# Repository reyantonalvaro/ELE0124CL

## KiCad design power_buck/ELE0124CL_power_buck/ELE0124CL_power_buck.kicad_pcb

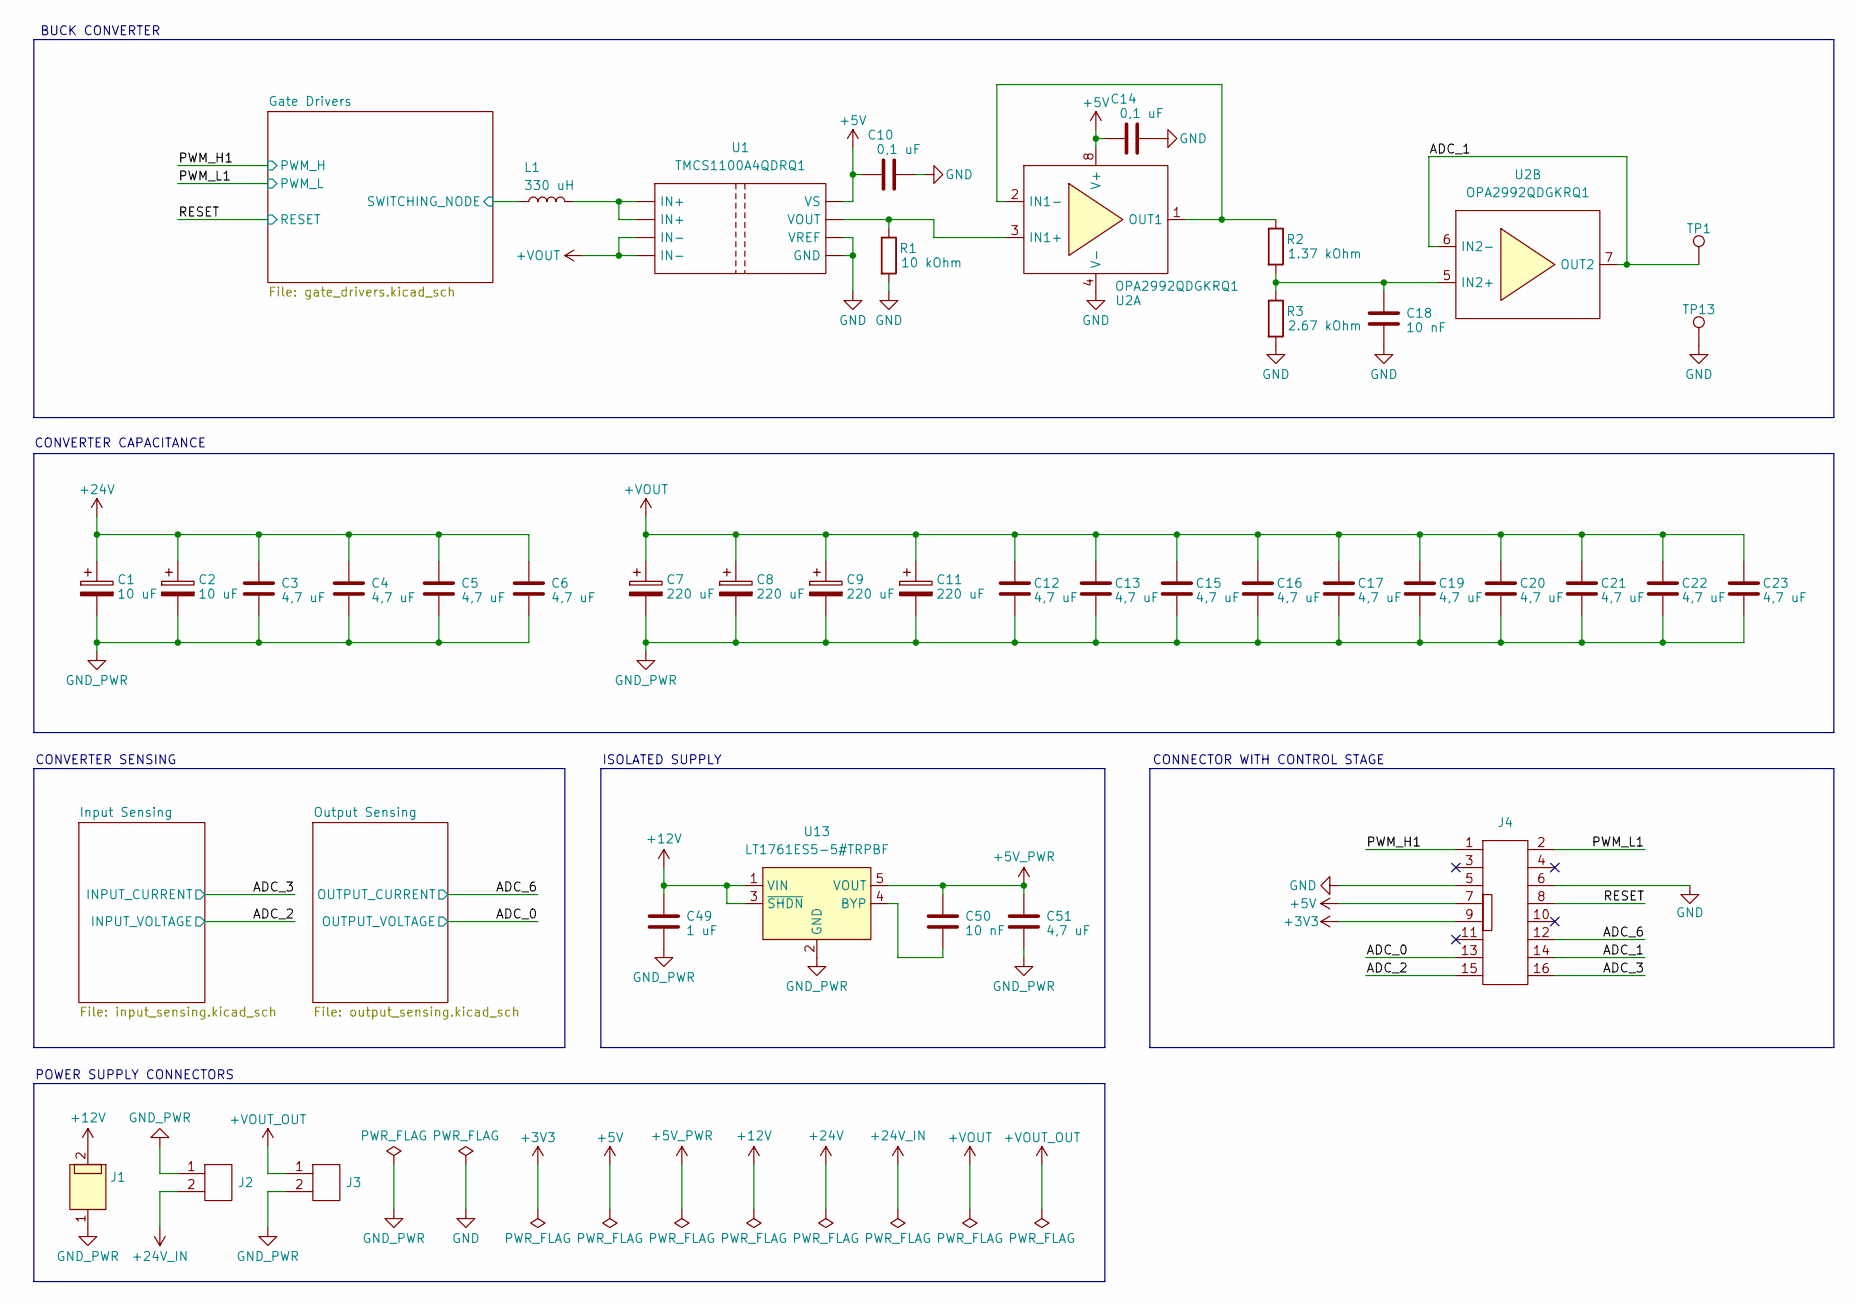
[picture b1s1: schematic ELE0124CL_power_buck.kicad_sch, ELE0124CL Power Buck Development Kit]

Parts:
C1, C2: 10 uF; C_D5.0mm_H11.0mm_P2.00mm
C3, C4, C5, C6, C12, C13, C15, C16, C17, C19, C20, C21, C22, C23, C51: 4,7 uF; C_1206_3216Metric
C7, C8, C9, C11: 220 uF; C_D10.0mm_H16.0mm_P5.00mm
C10, C14: 0,1 uF; C_0603_1608Metric
C18, C50: 10 nF; C_0603_1608Metric
C49: 1 uF; C_1206_3216Metric
J1: 43045-0212; CONN_SOCKET_1x02_P3.00mm_Vertical
J2, J3: MSTBVA 2,5/ 2-G-5,08; CONN_TERMINAL_BLOCK_1x02_P5.08mm_Vertical
J4: 878311620; CONN_SOCKET_2x08_P2.00mm_Vertical
L1: 330 uH; L_74437529203331
R1: 10 kOhm; R_0603_1608Metric
R2: 1.37 kOhm; R_0603_1608Metric
R3: 2.67 kOhm; R_0603_1608Metric
TP1, TP13: TP_THT
U1: TMCS1100A4QDRQ1; SOIC-8_5.40mm_P1.27mm
U2: OPA2992QDGKRQ1; VSSOP-8_4.40mm_P0.65mm
U13: LT1761ES5-5#TRPBF; TSOT-23-5

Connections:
+3V3: J4.9; also elsewhere on the board
+5V: C10.1, C14.1, J4.7, U1.8 (VS), U2.8 (V+); also elsewhere on the board
+5V_PWR: C50.1, C51.1, U13.5 (VOUT); also elsewhere on the board
+12V: C49.1, J1.2, U13.1 (VIN), U13.3 (~SHDN); also elsewhere on the board
+24V: C1.1, C2.1, C3.1, C4.1, C5.1, C6.1; also elsewhere on the board
+24V_IN: J2.2; also elsewhere on the board
+VOUT: C7.1, C8.1, C9.1, C11.1, C12.1, C13.1, C15.1, C16.1, C17.1, C19.1, C20.1, C21.1, C22.1, C23.1, U1.3 (IN-), U1.4 (IN-); also elsewhere on the board
+VOUT_OUT: J3.1; also elsewhere on the board
/ADC_0: J4.13; also elsewhere on the board
/ADC_1: J4.14, TP1.1 (TP), U2.6 (IN2-), U2.7 (OUT2)
/ADC_2: J4.15; also elsewhere on the board
/ADC_3: J4.16; also elsewhere on the board
/ADC_6: J4.12; also elsewhere on the board
/Gate Drivers/SWITCHING_NODE: L1.1; also elsewhere on the board
/PWM_H1: J4.1; also elsewhere on the board
/PWM_L1: J4.2; also elsewhere on the board
/RESET: J4.8; also elsewhere on the board
GND: C10.2, C14.2, C18.2, J4.5, J4.6, R1.2, R3.2, TP13.1 (TP), U1.5 (GND), U1.6 (VREF), U2.4 (V-); also elsewhere on the board
GND_PWR: C1.2, C2.2, C3.2, C4.2, C5.2, C6.2, C7.2, C8.2, C9.2, C11.2, C12.2, C13.2, C15.2, C16.2, C17.2, C19.2, C20.2, C21.2, C22.2, C23.2, C49.2, C51.2, J1.1, J2.1, J3.2, U13.2 (GND); also elsewhere on the board
unnamed: L1.2, U1.1 (IN+), U1.2 (IN+)
unnamed: R1.1, U1.7 (VOUT), U2.3 (IN1+)
unnamed: R2.1, U2.1 (OUT1), U2.2 (IN1-)
unnamed: C18.1, R2.2, R3.1, U2.5 (IN2+)
unnamed: C50.2, U13.4 (BYP)

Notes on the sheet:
CONNECTOR WITH CONTROL STAGE
CONVERTER CAPACITANCE
CONVERTER SENSING
BUCK CONVERTER
ISOLATED SUPPLY
POWER SUPPLY CONNECTORS

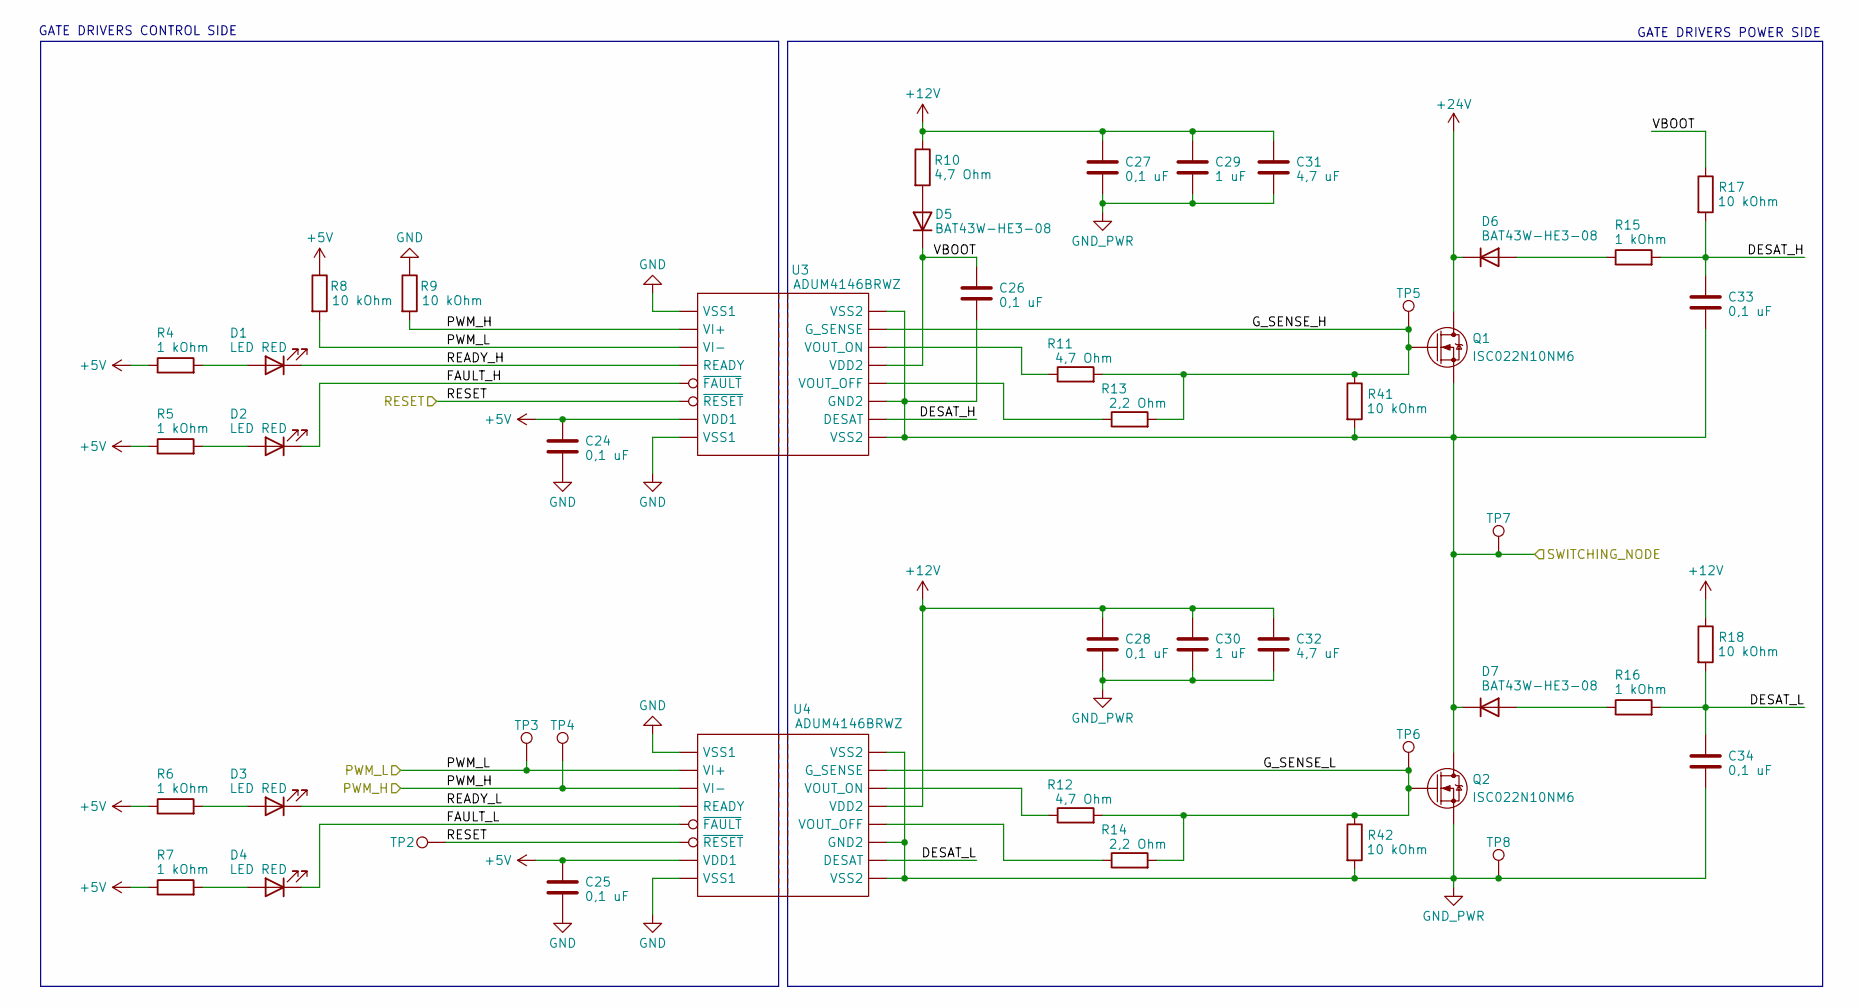
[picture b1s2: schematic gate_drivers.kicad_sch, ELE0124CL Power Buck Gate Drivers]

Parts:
C24, C25, C27, C28, C33, C34: 0,1 uF; C_0603_1608Metric
C26: 0,1 uF; C_1206_3216Metric
C29, C30: 1 uF; C_1206_3216Metric
C31, C32: 4,7 uF; C_1206_3216Metric
D1, D2, D3, D4: LED RED; D_0603_1608Metric
D5, D6, D7: BAT43W-HE3-08; D_SOD-123
Q1, Q2: ISC022N10NM6; PG-TDSON-8-3
R4, R5, R6, R7, R15, R16: 1 kOhm; R_0603_1608Metric
R8, R9, R17, R18, R41, R42: 10 kOhm; R_0603_1608Metric
R10, R11, R12: 4,7 Ohm; R_2512_6332Metric
R13, R14: 2,2 Ohm; R_2512_6332Metric
TP2, TP3, TP4: TP_D1.0mm
TP5, TP6, TP7, TP8: TP_THT
U3, U4: ADUM4146BRWZ; SOIC-16W_9.60mm_P1.27mm

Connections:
+5V: C24.1, C25.1, R4.1, R5.1, R6.1, R7.1, R8.1, U3.7 (VDD1), U4.7 (VDD1); also elsewhere on the board
+12V: C27.1, C28.1, C29.1, C30.1, C31.1, C32.1, R10.1, R18.1, U4.13 (VDD2); also elsewhere on the board
+24V: D6.1 (K), Q1.3 (D); also elsewhere on the board
/Gate Drivers/DESAT_H: C33.1, R15.2, R17.2, U3.10 (DESAT)
/Gate Drivers/DESAT_L: C34.1, R16.2, R18.2, U4.10 (DESAT)
/Gate Drivers/FAULT_H: D2.1 (K), U3.5 (~FAULT)
/Gate Drivers/FAULT_L: D4.1 (K), U4.5 (~FAULT)
/Gate Drivers/G_SENSE_H: Q1.2 (G), R11.2, R13.2, R41.1, TP5.1 (TP), U3.15 (G_SENSE)
/Gate Drivers/G_SENSE_L: Q2.2 (G), R12.2, R14.2, R42.1, TP6.1 (TP), U4.15 (G_SENSE)
/Gate Drivers/READY_H: D1.1 (K), U3.4 (READY)
/Gate Drivers/READY_L: D3.1 (K), U4.4 (READY)
/Gate Drivers/SWITCHING_NODE: C26.2, C33.2, D7.1 (K), Q1.1 (S), Q2.3 (D), R41.2, TP7.1 (TP), U3.9 (VSS2), U3.11 (GND2), U3.16 (VSS2); also elsewhere on the board
/Gate Drivers/VBOOT: C26.1, D5.1 (K), R17.1, U3.13 (VDD2)
/PWM_H1: R9.2, TP4.1 (TP), U3.2 (VI+), U4.3 (VI-); also elsewhere on the board
/PWM_L1: R8.2, TP3.1 (TP), U3.3 (VI-), U4.2 (VI+); also elsewhere on the board
/RESET: TP2.1 (TP), U3.6 (~RESET), U4.6 (~RESET); also elsewhere on the board
GND: C24.2, C25.2, R9.1, U3.1 (VSS1), U3.8 (VSS1), U4.1 (VSS1), U4.8 (VSS1); also elsewhere on the board
GND_PWR: C27.2, C28.2, C29.2, C30.2, C31.2, C32.2, C34.2, Q2.1 (S), R42.2, TP8.1 (TP), U4.9 (VSS2), U4.11 (GND2), U4.16 (VSS2); also elsewhere on the board
unnamed: D1.2 (A), R4.2
unnamed: D2.2 (A), R5.2
unnamed: D3.2 (A), R6.2
unnamed: D4.2 (A), R7.2
unnamed: D5.2 (A), R10.2
unnamed: D6.2 (A), R15.1
unnamed: D7.2 (A), R16.1
unnamed: R13.1, U3.12 (VOUT_OFF)
unnamed: R11.1, U3.14 (VOUT_ON)
unnamed: R14.1, U4.12 (VOUT_OFF)
unnamed: R12.1, U4.14 (VOUT_ON)

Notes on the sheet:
GATE DRIVERS CONTROL SIDE
GATE DRIVERS POWER SIDE

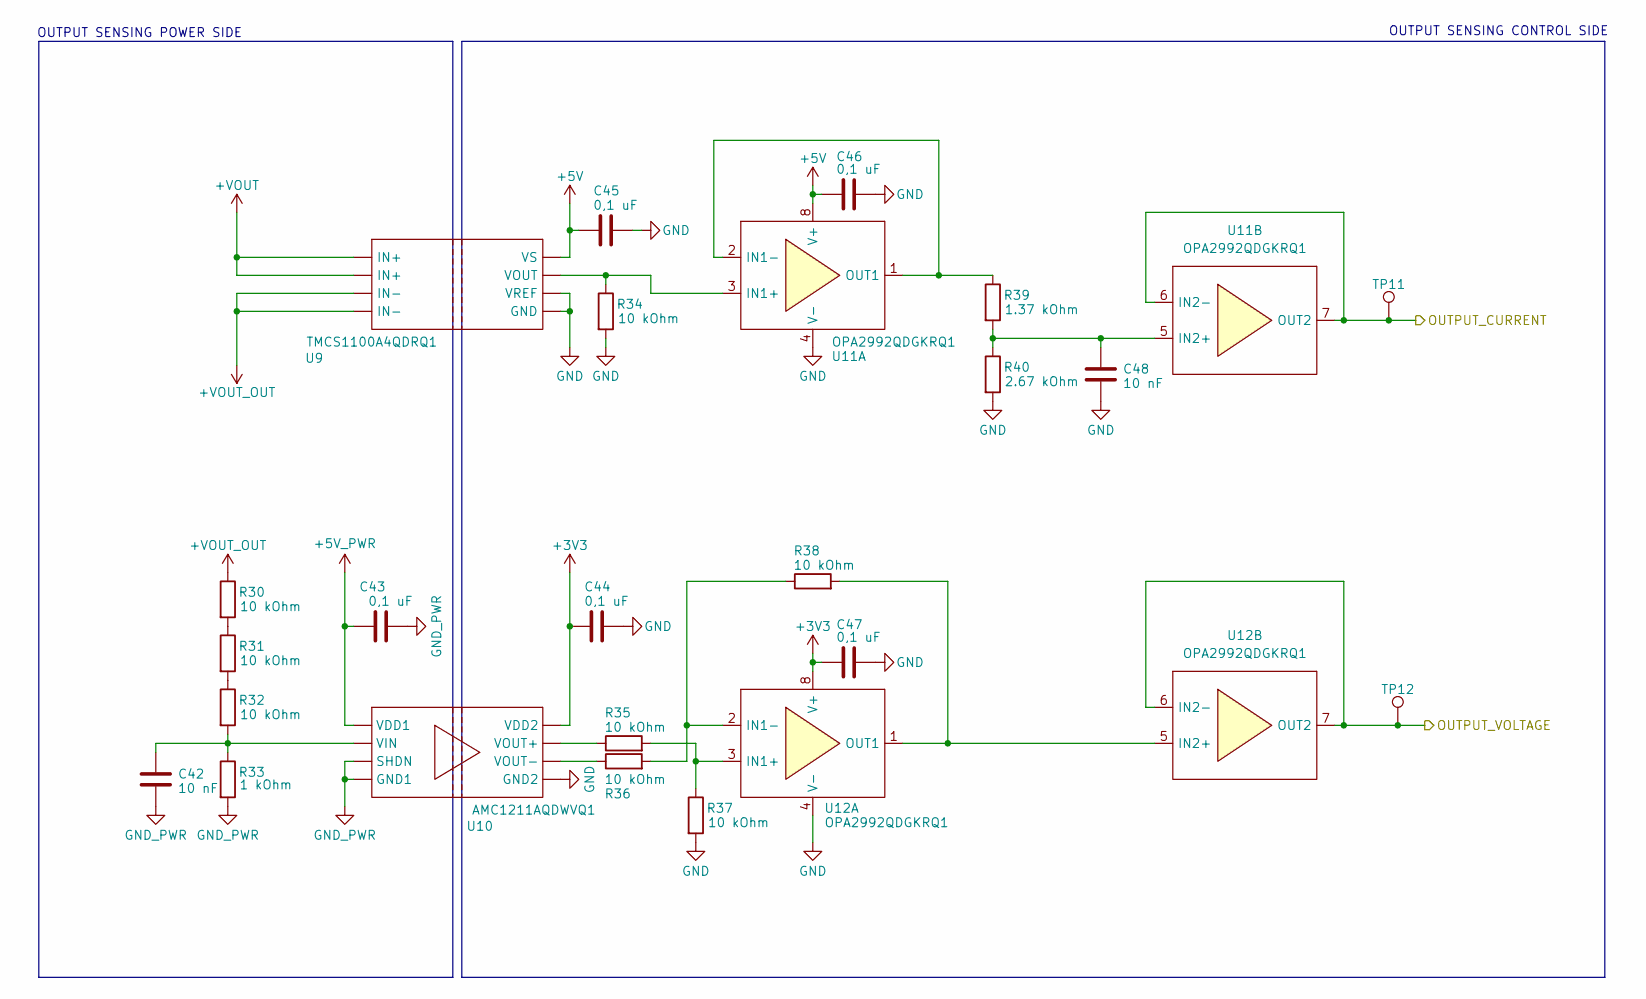
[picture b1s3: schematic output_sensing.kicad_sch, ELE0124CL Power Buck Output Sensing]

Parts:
C42, C48: 10 nF; C_0603_1608Metric
C43, C44, C45, C46, C47: 0,1 uF; C_0603_1608Metric
R30, R31, R32, R34, R35, R36, R37, R38: 10 kOhm; R_0603_1608Metric
R33: 1 kOhm; R_0603_1608Metric
R39: 1.37 kOhm; R_0603_1608Metric
R40: 2.67 kOhm; R_0603_1608Metric
TP11, TP12: TP_D1.0mm
U9: TMCS1100A4QDRQ1; SOIC-8_5.40mm_P1.27mm
U10: AMC1211AQDWVQ1; SSO-8_10.80mm_P1.27mm
U11, U12: OPA2992QDGKRQ1; VSSOP-8_4.40mm_P0.65mm

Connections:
+3V3: C44.1, C47.1, U10.8 (VDD2), U12.8 (V+); also elsewhere on the board
+5V: C45.1, C46.1, U9.8 (VS), U11.8 (V+); also elsewhere on the board
+5V_PWR: C43.1, U10.1 (VDD1); also elsewhere on the board
+VOUT: U9.1 (IN+), U9.2 (IN+); also elsewhere on the board
+VOUT_OUT: R30.1, U9.3 (IN-), U9.4 (IN-); also elsewhere on the board
/ADC_0: TP12.1 (TP), U12.6 (IN2-), U12.7 (OUT2); also elsewhere on the board
/ADC_6: TP11.1 (TP), U11.6 (IN2-), U11.7 (OUT2); also elsewhere on the board
GND: C44.2, C45.2, C46.2, C47.2, C48.2, R34.2, R37.2, R40.2, U9.5 (GND), U9.6 (VREF), U10.5 (GND2), U11.4 (V-), U12.4 (V-); also elsewhere on the board
GND_PWR: C42.2, C43.2, R33.2, U10.3 (SHDN), U10.4 (GND1); also elsewhere on the board
unnamed: R30.2, R31.1
unnamed: R31.2, R32.1
unnamed: C42.1, R32.2, R33.1, U10.2 (VIN)
unnamed: R35.1, U10.7 (VOUT+)
unnamed: R36.1, U10.6 (VOUT-)
unnamed: R34.1, U9.7 (VOUT), U11.3 (IN1+)
unnamed: R39.1, U11.1 (OUT1), U11.2 (IN1-)
unnamed: C48.1, R39.2, R40.1, U11.5 (IN2+)
unnamed: R35.2, R37.1, U12.3 (IN1+)
unnamed: R36.2, R38.1, U12.2 (IN1-)
unnamed: R38.2, U12.1 (OUT1), U12.5 (IN2+)

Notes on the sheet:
OUTPUT SENSING POWER SIDE
OUTPUT SENSING CONTROL SIDE

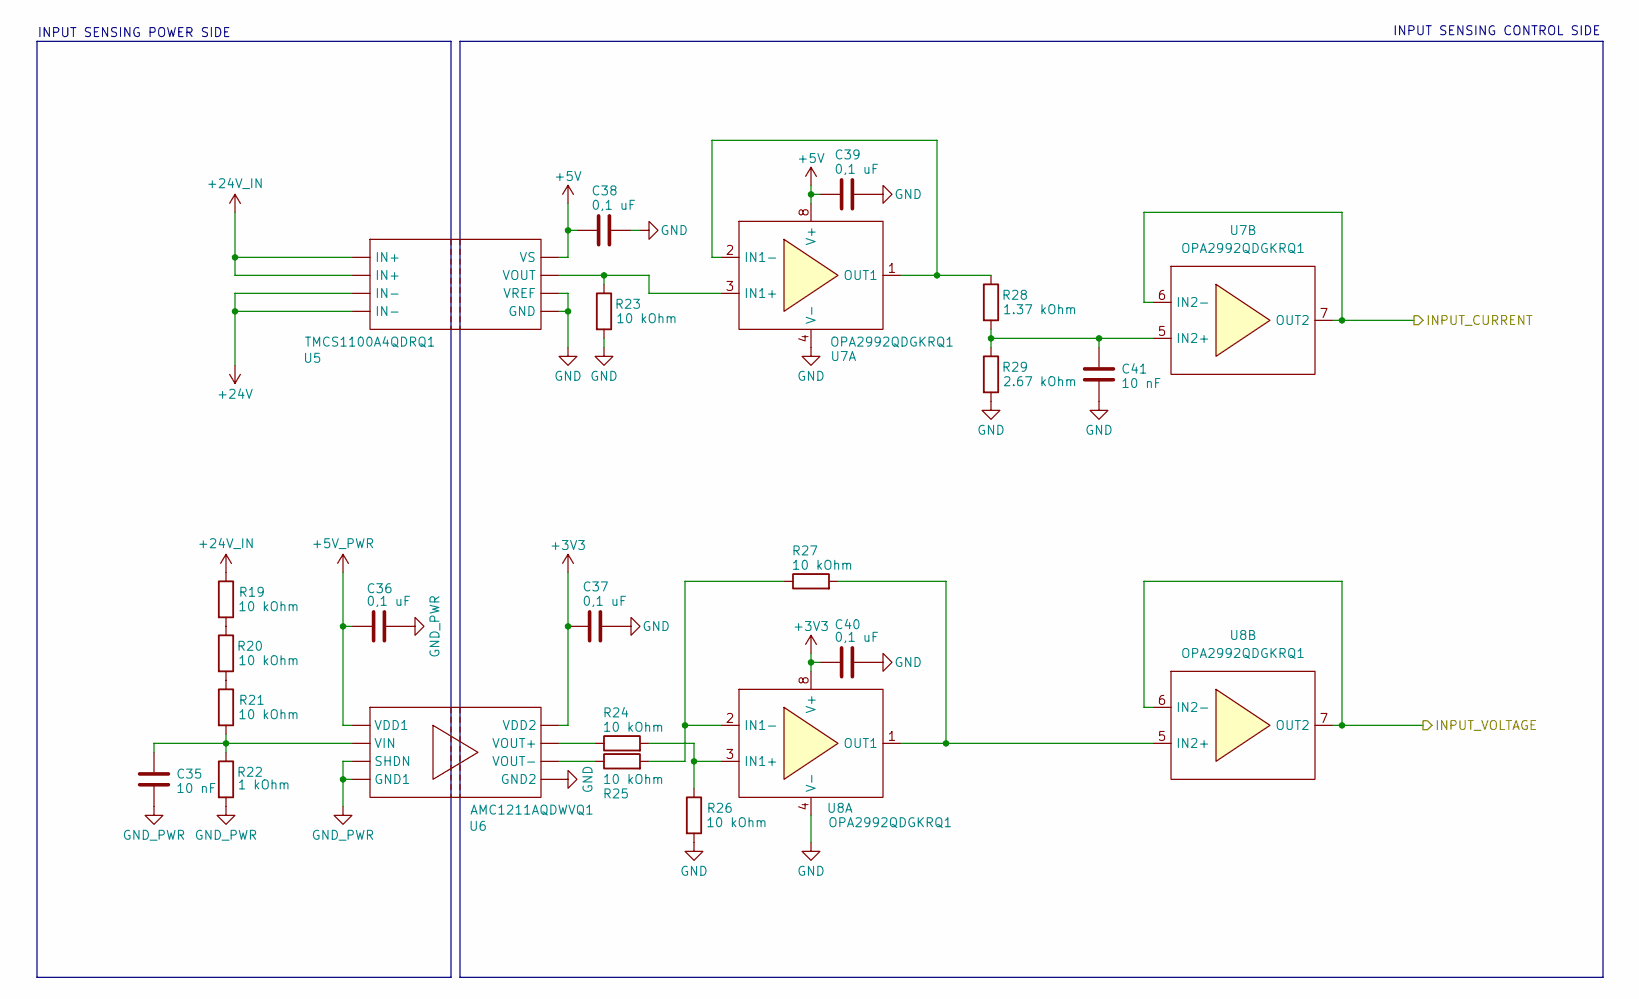
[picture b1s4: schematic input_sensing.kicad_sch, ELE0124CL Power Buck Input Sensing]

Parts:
C35, C41: 10 nF; C_0603_1608Metric
C36, C37, C38, C39, C40: 0,1 uF; C_0603_1608Metric
R19, R20, R21, R23, R24, R25, R26, R27: 10 kOhm; R_0603_1608Metric
R22: 1 kOhm; R_0603_1608Metric
R28: 1.37 kOhm; R_0603_1608Metric
R29: 2.67 kOhm; R_0603_1608Metric
U5: TMCS1100A4QDRQ1; SOIC-8_5.40mm_P1.27mm
U6: AMC1211AQDWVQ1; SSO-8_10.80mm_P1.27mm
U7, U8: OPA2992QDGKRQ1; VSSOP-8_4.40mm_P0.65mm

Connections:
+3V3: C37.1, C40.1, U6.8 (VDD2), U8.8 (V+); also elsewhere on the board
+5V: C38.1, C39.1, U5.8 (VS), U7.8 (V+); also elsewhere on the board
+5V_PWR: C36.1, U6.1 (VDD1); also elsewhere on the board
+24V: U5.3 (IN-), U5.4 (IN-); also elsewhere on the board
+24V_IN: R19.1, U5.1 (IN+), U5.2 (IN+); also elsewhere on the board
/ADC_2: U8.6 (IN2-), U8.7 (OUT2); also elsewhere on the board
/ADC_3: U7.6 (IN2-), U7.7 (OUT2); also elsewhere on the board
GND: C37.2, C38.2, C39.2, C40.2, C41.2, R23.2, R26.2, R29.2, U5.5 (GND), U5.6 (VREF), U6.5 (GND2), U7.4 (V-), U8.4 (V-); also elsewhere on the board
GND_PWR: C35.2, C36.2, R22.2, U6.3 (SHDN), U6.4 (GND1); also elsewhere on the board
unnamed: R19.2, R20.1
unnamed: R20.2, R21.1
unnamed: R23.1, U5.7 (VOUT), U7.3 (IN1+)
unnamed: C35.1, R21.2, R22.1, U6.2 (VIN)
unnamed: R24.1, U6.7 (VOUT+)
unnamed: R25.1, U6.6 (VOUT-)
unnamed: R28.1, U7.1 (OUT1), U7.2 (IN1-)
unnamed: C41.1, R28.2, R29.1, U7.5 (IN2+)
unnamed: R24.2, R26.1, U8.3 (IN1+)
unnamed: R25.2, R27.1, U8.2 (IN1-)
unnamed: R27.2, U8.1 (OUT1), U8.5 (IN2+)

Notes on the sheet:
INPUT SENSING POWER SIDE
INPUT SENSING CONTROL SIDE

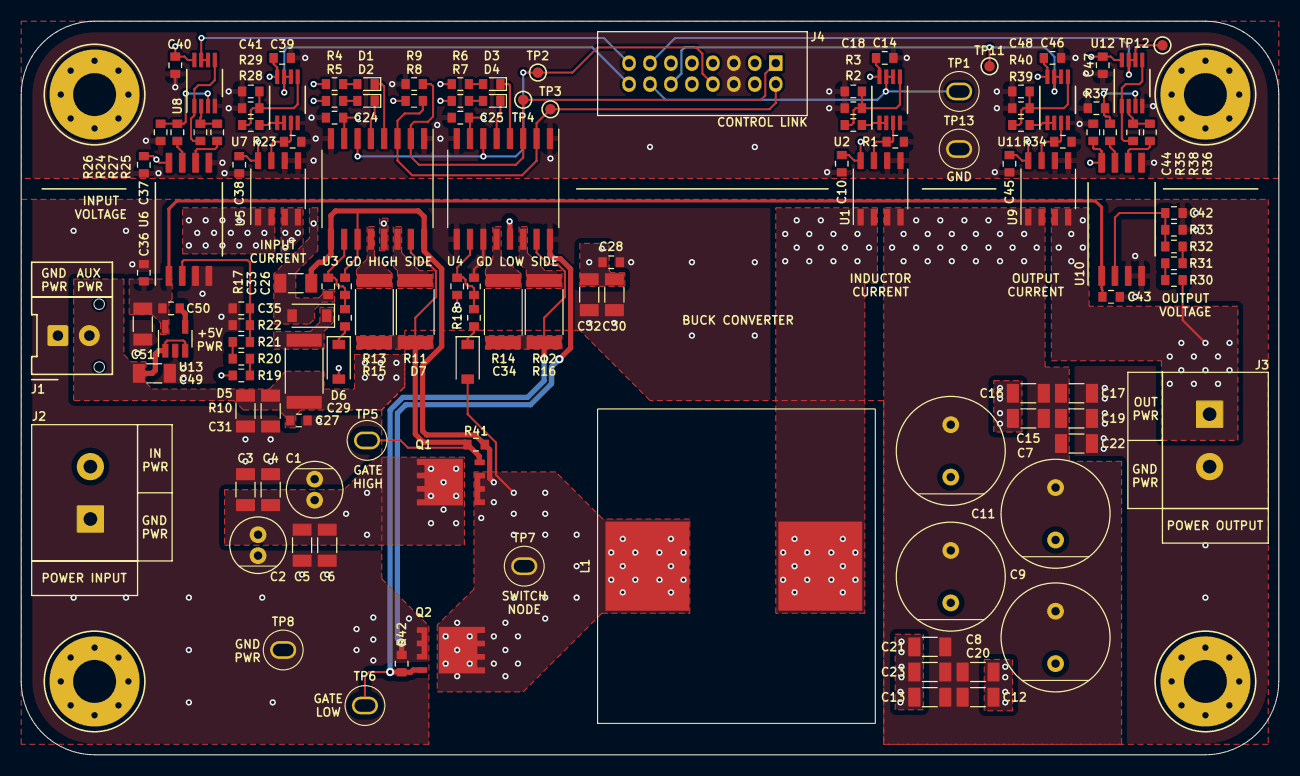
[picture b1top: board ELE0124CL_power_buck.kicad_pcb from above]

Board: 4 copper layers, 120.0 x 70.0 mm, 131 parts (0 on the bottom side), 66 nets.

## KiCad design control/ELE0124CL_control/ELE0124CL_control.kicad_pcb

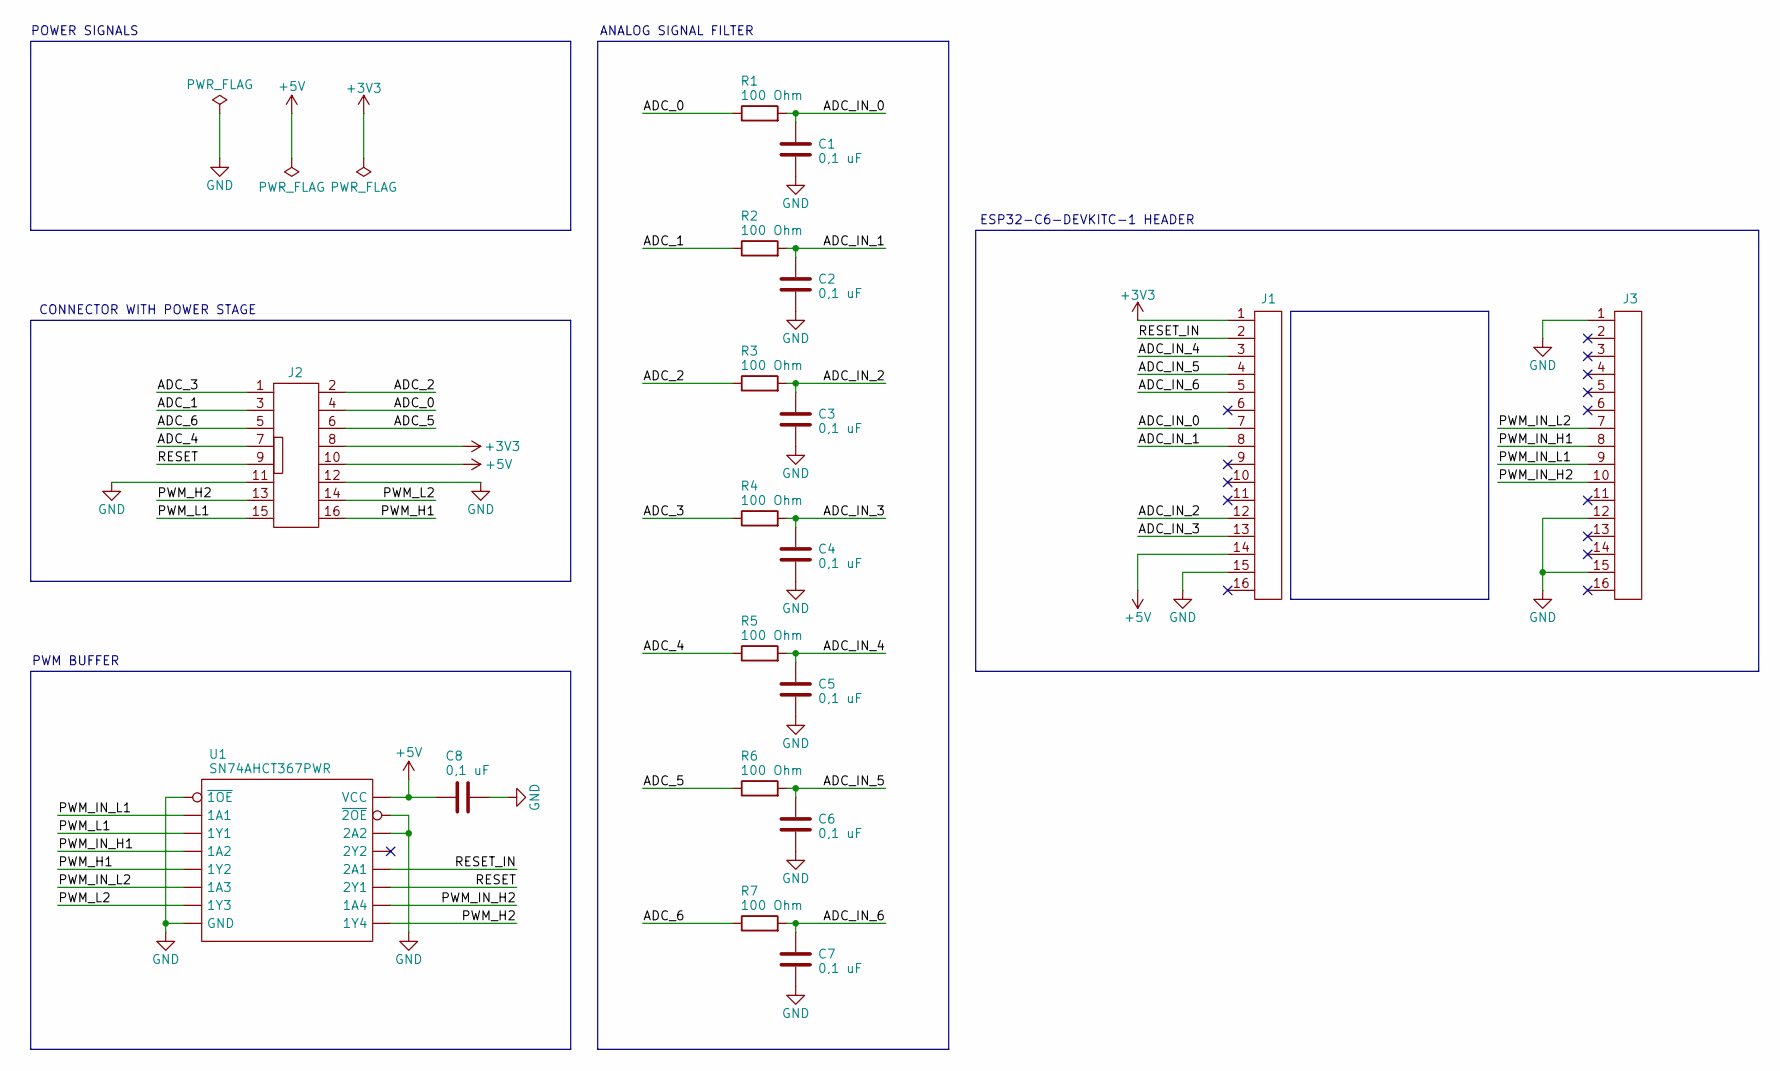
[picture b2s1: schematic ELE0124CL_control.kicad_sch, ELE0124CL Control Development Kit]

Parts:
C1, C2, C3, C4, C5, C6, C7, C8: 0,1 uF; C_0603_1608Metric
J1, J3: M20-7821646; CONN_SOCKET_1x16_P2.54mm_Vertical
J2: 878311620; CONN_SOCKET_2x08_P2.00mm_Vertical
R1, R2, R3, R4, R5, R6, R7: 100 Ohm; R_0603_1608Metric
U1: SN74AHCT367PWR; TSSOP-16_5.80mm_P0.65mm

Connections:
+3V3: J1.1, J2.8
+5V: C8.1, J1.14, J2.10, U1.16 (VCC)
/ADC_0: J2.4, R1.1
/ADC_1: J2.3, R2.1
/ADC_2: J2.2, R3.1
/ADC_3: J2.1, R4.1
/ADC_4: J2.7, R5.1
/ADC_5: J2.6, R6.1
/ADC_6: J2.5, R7.1
/ADC_IN_0: C1.1, J1.7, R1.2
/ADC_IN_1: C2.1, J1.8, R2.2
/ADC_IN_2: C3.1, J1.12, R3.2
/ADC_IN_3: C4.1, J1.13, R4.2
/ADC_IN_4: C5.1, J1.3, R5.2
/ADC_IN_5: C6.1, J1.4, R6.2
/ADC_IN_6: C7.1, J1.5, R7.2
/PWM_H1: J2.16, U1.5 (1Y2)
/PWM_H2: J2.13, U1.9 (1Y4)
/PWM_IN_H1: J3.8, U1.4 (1A2)
/PWM_IN_H2: J3.10, U1.10 (1A4)
/PWM_IN_L1: J3.9, U1.2 (1A1)
/PWM_IN_L2: J3.7, U1.6 (1A3)
/PWM_L1: J2.15, U1.3 (1Y1)
/PWM_L2: J2.14, U1.7 (1Y3)
/RESET: J2.9, U1.11 (2Y1)
/RESET_IN: J1.2, U1.12 (2A1)
GND: C1.2, C2.2, C3.2, C4.2, C5.2, C6.2, C7.2, C8.2, J1.15, J2.11, J2.12, J3.1, J3.12, J3.15, U1.1 (~1OE), U1.8 (GND), U1.14 (2A2), U1.15 (~2OE)

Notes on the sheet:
CONNECTOR WITH POWER STAGE
ESP32-C6-DEVKITC-1 HEADER
PWM BUFFER
ANALOG SIGNAL FILTER
POWER SIGNALS

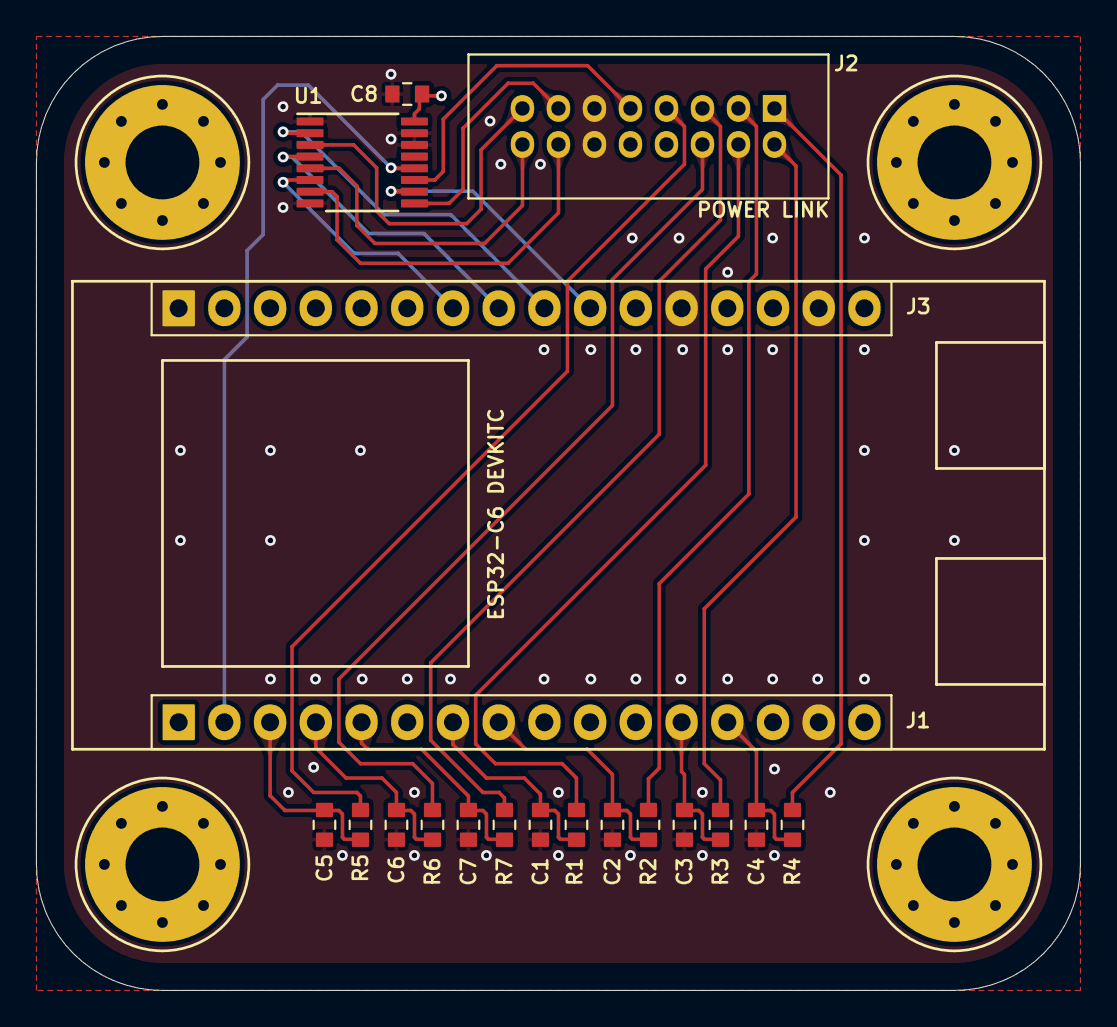
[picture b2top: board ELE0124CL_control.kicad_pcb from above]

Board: 4 copper layers, 58.0 x 53.0 mm, 19 parts (0 on the bottom side), 27 nets.

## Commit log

2024-08-10 PCB version 1.0
